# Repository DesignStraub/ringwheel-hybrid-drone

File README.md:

# Ringwheel – a drone whose prop ducts become wheels

A 5-inch FPV quadcopter that lands, folds its four ducts down by 90° and drives away on them. Each duct ring has a tread and turns into a wheel. The same four motors fly the drone and drive the wheels.

> **Status: design study.** Nothing here has been built, printed or flown yet. All dimensions, gear meshes and PCB traces are unverified until someone builds it. If you do, please open an issue and tell me what broke.

| Flight mode | Drive mode |
|---|---|
|  |  |

**Video:** [Watch the 55-second walkthrough on YouTube](https://www.youtube.com/shorts/o1WtWeNPCIw) or download it in 16:9 as [MP4](docs/video/ringwheel.mp4) (17 MB)

## How it works

- **Folding:** Each arm ends in a hinge. A small N20 gear motor turns it through a self-locking brass worm drive (1:30). An AS5600 magnetic sensor reads the angle, and fixed end stops limit the travel to 0° (flight) and 90° (drive).
- **Ring = wheel:** The duct around each 5.1" propeller has a TPU tread and runs on the hollow axle. In flight the ring is locked.
- **Drive train:** A sliding coupler on each motor axle switches between two positions. A solenoid coil pulls it one way, a spring pushes it back.
  - **Flight:** The coupler locks the wheel hub, so the ring stands still around the spinning prop.
  - **Drive:** The coupler engages the motor bell and drives the wheel through a 1:4 planetary stage (module 0.7, 24/24/72 teeth) inside the hub.
  - A Hall sensor (AH1806) and a small ring magnet confirm the coupler position.
- **Electronics:** A custom board (Hybrid-Controller HC-1, ESP32-S3) sits between the flight controller and the 4-in-1 ESC. A bus switch hands the four DShot signals either to the flight controller (flight) or to the ESP32 (drive). The board also runs the hinge motors and the solenoids. One small corner board per hinge (EP-1) carries the angle sensor and the wiring through the joint.
- **Safety logic:** Drive mode is only allowed while the flight controller reports *disarmed* and all four couplers report *engaged*. Folding only happens at standstill. See [electronics/README_Elektronik.md](electronics/README_Elektronik.md) (German) for the full sequence and pin map.

## Key data (from CAD)

| | |
|---|---|
| Props | 5.1" three-blade (Gemfan Hurricane 51466-3), duct inner Ø 130 mm |
| Motors | 4× 2306 2450 KV, 4S |
| Flight stack | 30 × 30 F722 + 55 A 4-in-1 ESC (Flywoo GOKU), ELRS receiver |
| Battery | 4S 1300 mAh |
| FPV | DJI O4 Air Unit Lite, camera in the wedge nose, tilted 15° |
| Hinge spacing | 170 × 160 mm |
| Mass | ≈ 950 g as modelled |
| Print materials | PA6-GF (frame, gears), TPU 95A (treads) |
| Parts cost | ≈ 910 € for the drone, ≈ 1,340 € including goggles, radio and charger (Germany, October 2026) |

## What is in this repository

| Path | Content |
|---|---|
| `cad/Drohne_Hybid_Car_v15.f3d` | Current Fusion design with joints and parameters (`klappwinkel` = fold angle, `muffe_weg` = coupler travel) |
| `cad/Drohne_Hybid_Car_v15.step` | The same assembly as STEP for other CAD tools |
| `cad/Drohne_Hybid_Car_v11_rounded_hull.f3d` | Older alternative with a rounded hull instead of the wedge nose |
| `electronics/` | KiCad 10 projects for HC-1 and EP-1, schematics as PDF, 3D models |
| `electronics/Fertigung/` | Gerber, BOM and placement files for JLCPCB |
| `docs/Kostenliste.md` | Full parts list with shop links and prices (German) |
| `docs/video/ringwheel.mp4` | Narrated walkthrough rendered from the Fusion model |

The detailed docs are in German for now. Translations are welcome.

## Open points before anyone builds it

- **Firmware:** not written yet. The ESP32 logic and the flight controller setup are only specified in the electronics README.
- **Flight performance:** untested. The ducts and the drive train add weight, so the thrust-to-weight ratio needs a real measurement.
- **Gear teeth:** module 0.7 in PA6-GF should print with a 0.4 mm nozzle, but this needs a test print.
- **Hall sensor:** the energised solenoid may trigger the sensor. This needs a bench test, which is why the firmware also checks the coupler via motor RPM.
- **Camera mount:** published dimensions of the O4 Lite camera disagree. The mount has slots to compensate, but check it against the real part.
- **PCBs:** routing was generated automatically and passes DRC, but review it in KiCad before ordering, especially USB and the power paths. Match the ESC connector pinout to the stack you buy.

## Credits

- Inspired by [Michael Rechtin's transforming drone](https://www.youtube.com/watch?v=f1GSzysrYtw). No files from his project are used here.
- CAD modelling, PCB layout and documentation were done with heavy AI assistance (Claude by Anthropic). That is one more reason to check every dimension before printing.
- Video narration generated with ElevenLabs (voice "Roger").
- Footprints and 3D models from the KiCad libraries remain under their own license. Product names belong to their respective owners.

## License

© 2026 DesignStraub. Licensed under [CC BY-NC-SA 4.0](LICENSE): you may build, modify and share this design for non-commercial purposes, as long as you give credit and share your changes under the same license.

**Additional permissions** granted by the author on top of the license:

- You may publish videos, photos and articles about your own build, including monetised ones (ads, sponsorships). This does not cover selling files, kits, parts or finished drones.
- Schools, universities, makerspaces and non-profit clubs may use the design for teaching and workshops, including fees that only cover material costs.
- **Commercial use** (selling kits, parts or built drones, or using the design in a product): please ask first by opening an issue.

## Safety and legal

This design is provided as is, without any warranty. Building, flying and driving it is entirely at your own risk.

- LiPo batteries can catch fire. Charge them under supervision and store them in a fireproof bag.
- The props sit on the drive motors, so they also spin in drive mode. Keep fingers out of the ducts.
- In the EU, a privately built drone of this weight falls into the open category, subcategory A3. You need to register as an operator, pass the A1/A3 online test, keep away from people and stay 150 m from residential areas. FPV flight requires an observer next to you. In Germany, liability insurance is mandatory. Check the rules in your country before the first flight.

---

## Kurz auf Deutsch

Eine 5-Zoll-FPV-Drohne, deren Propellerringe nach der Landung um 90° nach unten klappen und zu Rädern werden. Dieselben vier Motoren treiben beim Fahren über eine Schaltmuffe und ein Planetengetriebe 1:4 die Räder an. Das Projekt ist eine Konstruktionsstudie und noch nicht gebaut. Die ausführliche Doku zu Elektronik und Kosten ist auf Deutsch: [electronics/README_Elektronik.md](electronics/README_Elektronik.md) und [docs/Kostenliste.md](docs/Kostenliste.md).

Lizenz: CC BY-NC-SA 4.0 mit den oben genannten Zusatzerlaubnissen. Privat nachbauen und verändern ist ausdrücklich erwünscht. Für kommerzielle Nutzung bitte vorher fragen.

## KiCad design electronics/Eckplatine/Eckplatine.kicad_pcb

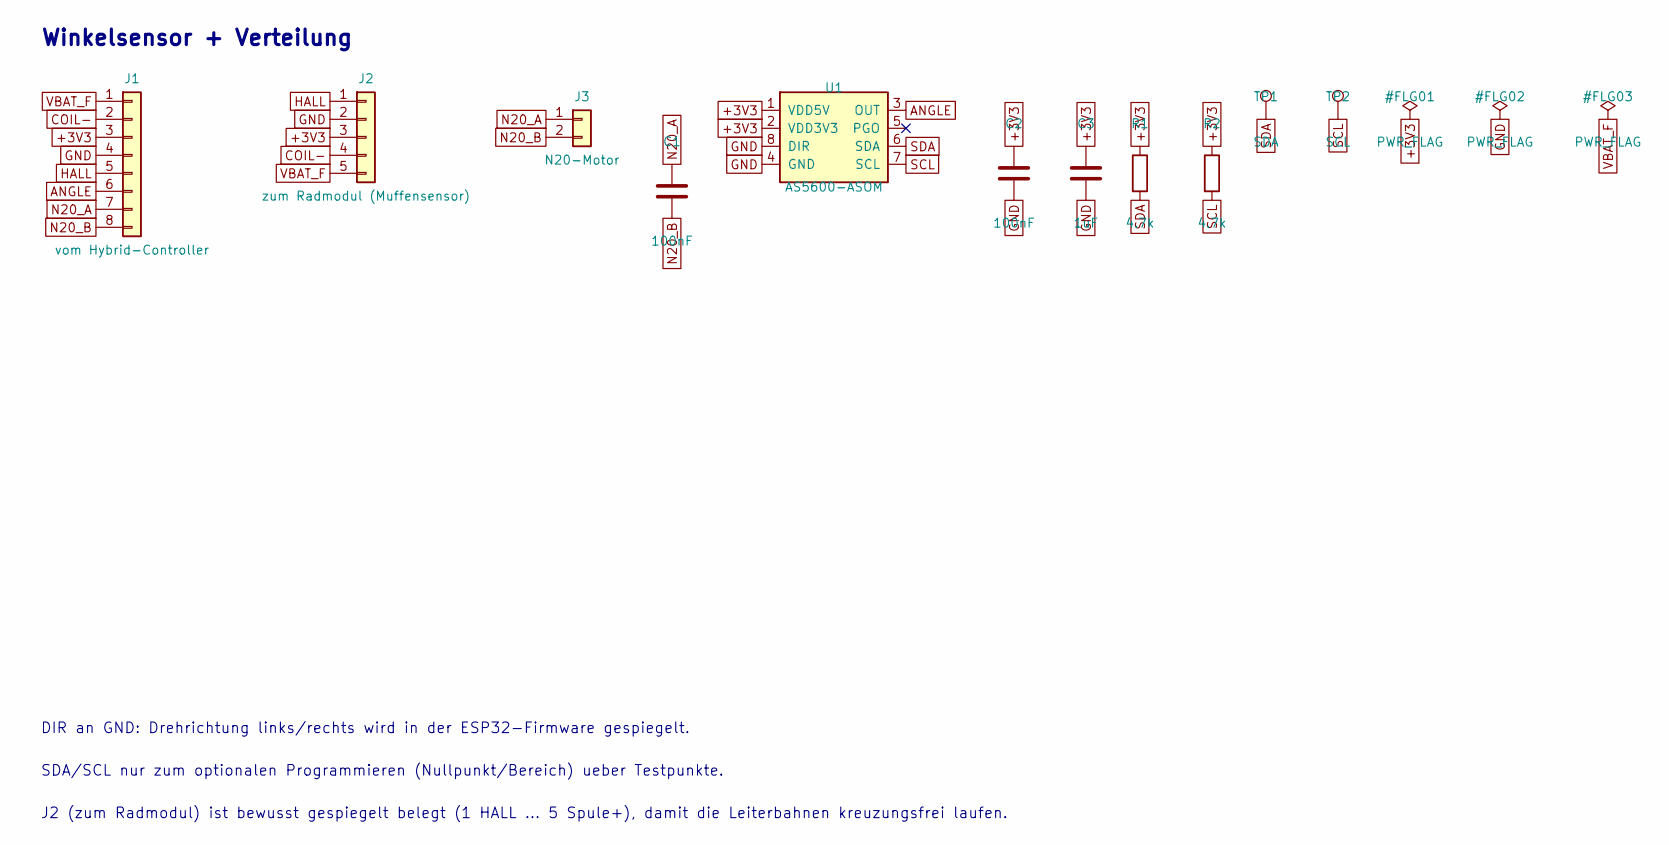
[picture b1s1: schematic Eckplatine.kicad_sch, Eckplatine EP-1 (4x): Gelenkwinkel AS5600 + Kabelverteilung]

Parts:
C1: 100nF; C_0603_1608Metric
C2: 100nF; C_0402_1005Metric
C3: 1uF; C_0402_1005Metric
J1: vom Hybrid-Controller; JST_GH_SM08B-GHS-TB_1x08-1MP_P1.25mm_Horizontal
J2: zum Radmodul (Muffensensor); JST_GH_SM05B-GHS-TB_1x05-1MP_P1.25mm_Horizontal
J3: N20-Motor; SolderWire-0.15sqmm_1x02_P4mm_D0.5mm_OD1.5mm
R1, R2: 4.7k; R_0402_1005Metric
TP1: SDA; TestPoint_Pad_D1.0mm
TP2: SCL; TestPoint_Pad_D1.0mm
U1: AS5600-ASOM; SOIC-8_3.9x4.9mm_P1.27mm

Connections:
+3V3: C2.1, C3.1, J1.3, J2.3, R1.1, R2.1, U1.1 (VDD5V), U1.2 (VDD3V3)
ANGLE: J1.6, U1.3 (OUT)
COIL-: J1.2, J2.4
GND: C2.2, C3.2, J1.4, J2.2, U1.4 (GND), U1.8 (DIR)
HALL: J1.5, J2.1
N20_A: C1.1, J1.7, J3.1
N20_B: C1.2, J1.8, J3.2
SCL: R2.2, TP2.1, U1.7 (SCL)
SDA: R1.2, TP1.1, U1.6 (SDA)
VBAT_F: J1.1, J2.5

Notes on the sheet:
Winkelsensor + Verteilung
J2 (zum Radmodul) ist bewusst gespiegelt belegt (1 HALL ... 5 Spule+), damit die Leiterbahnen kreuzungsfrei laufen.
DIR an GND: Drehrichtung links/rechts wird in der ESP32-Firmware gespiegelt.
SDA/SCL nur zum optionalen Programmieren (Nullpunkt/Bereich) ueber Testpunkte.

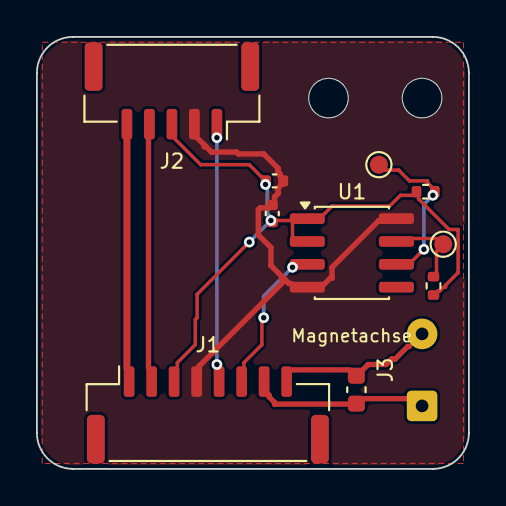
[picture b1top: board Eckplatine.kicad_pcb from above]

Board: 2 copper layers, 24.0 x 24.0 mm, 13 parts (0 on the bottom side), 10 nets.

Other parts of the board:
H1, H2: MountingHole_2.2mm_M2

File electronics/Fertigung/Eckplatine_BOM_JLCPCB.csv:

Comment,Designator,Footprint,LCSC Part #
100nF,C1,C_0603_1608Metric,
100nF,C2,C_0402_1005Metric,
1uF,C3,C_0402_1005Metric,
vom Hybrid-Controller,J1,JST_GH_SM08B-GHS-TB_1x08-1MP_P1.25mm_Horizontal,C265111
zum Radmodul (Muffensensor),J2,JST_GH_SM05B-GHS-TB_1x05-1MP_P1.25mm_Horizontal,C189896
4.7k,"R1,R2",R_0402_1005Metric,
AS5600-ASOM,U1,SOIC-8_3.9x4.9mm_P1.27mm,C79815

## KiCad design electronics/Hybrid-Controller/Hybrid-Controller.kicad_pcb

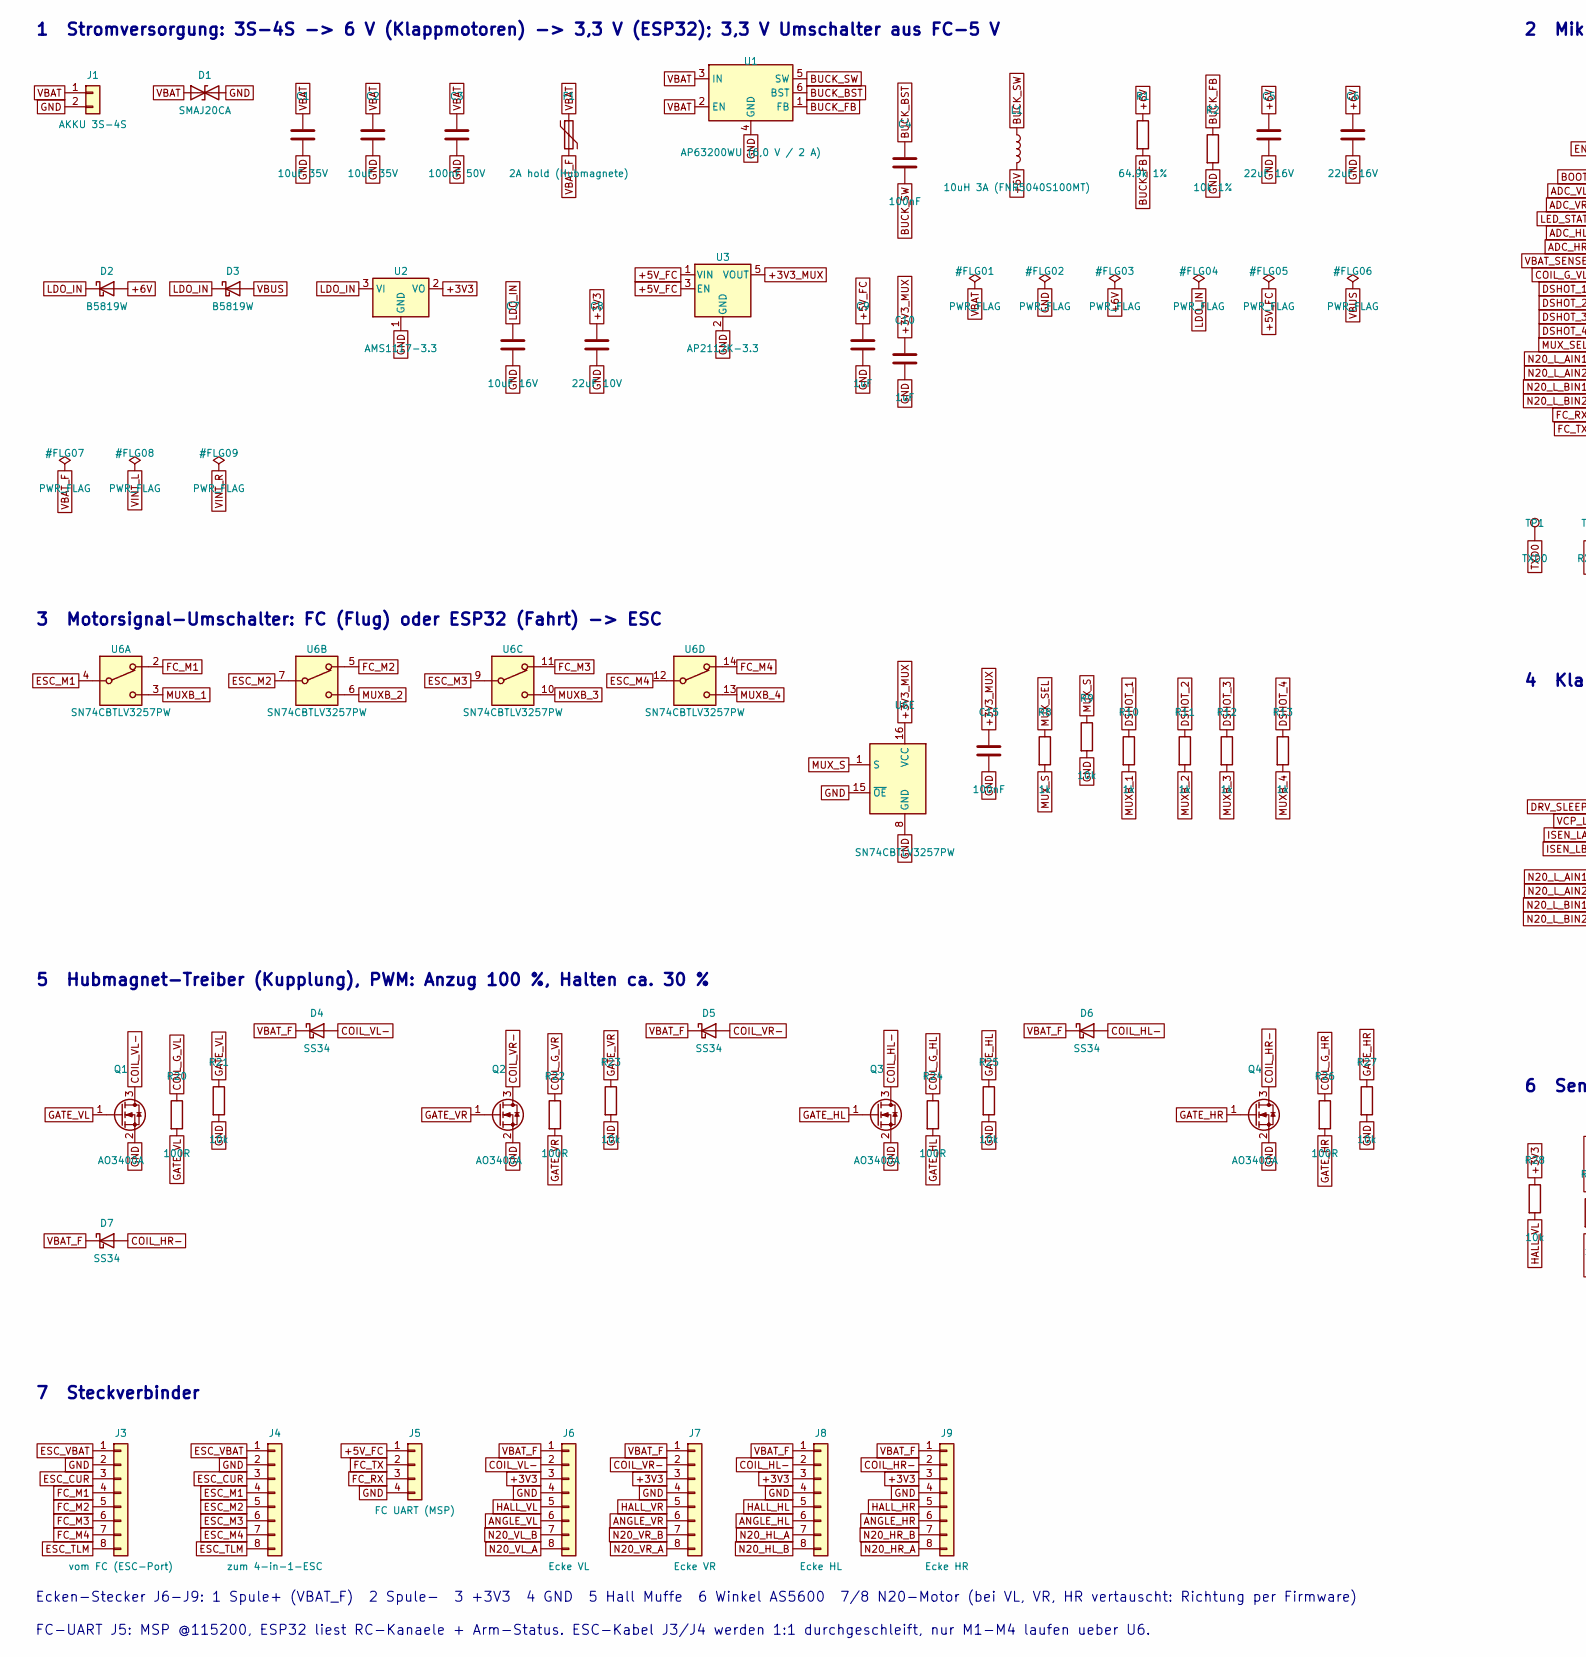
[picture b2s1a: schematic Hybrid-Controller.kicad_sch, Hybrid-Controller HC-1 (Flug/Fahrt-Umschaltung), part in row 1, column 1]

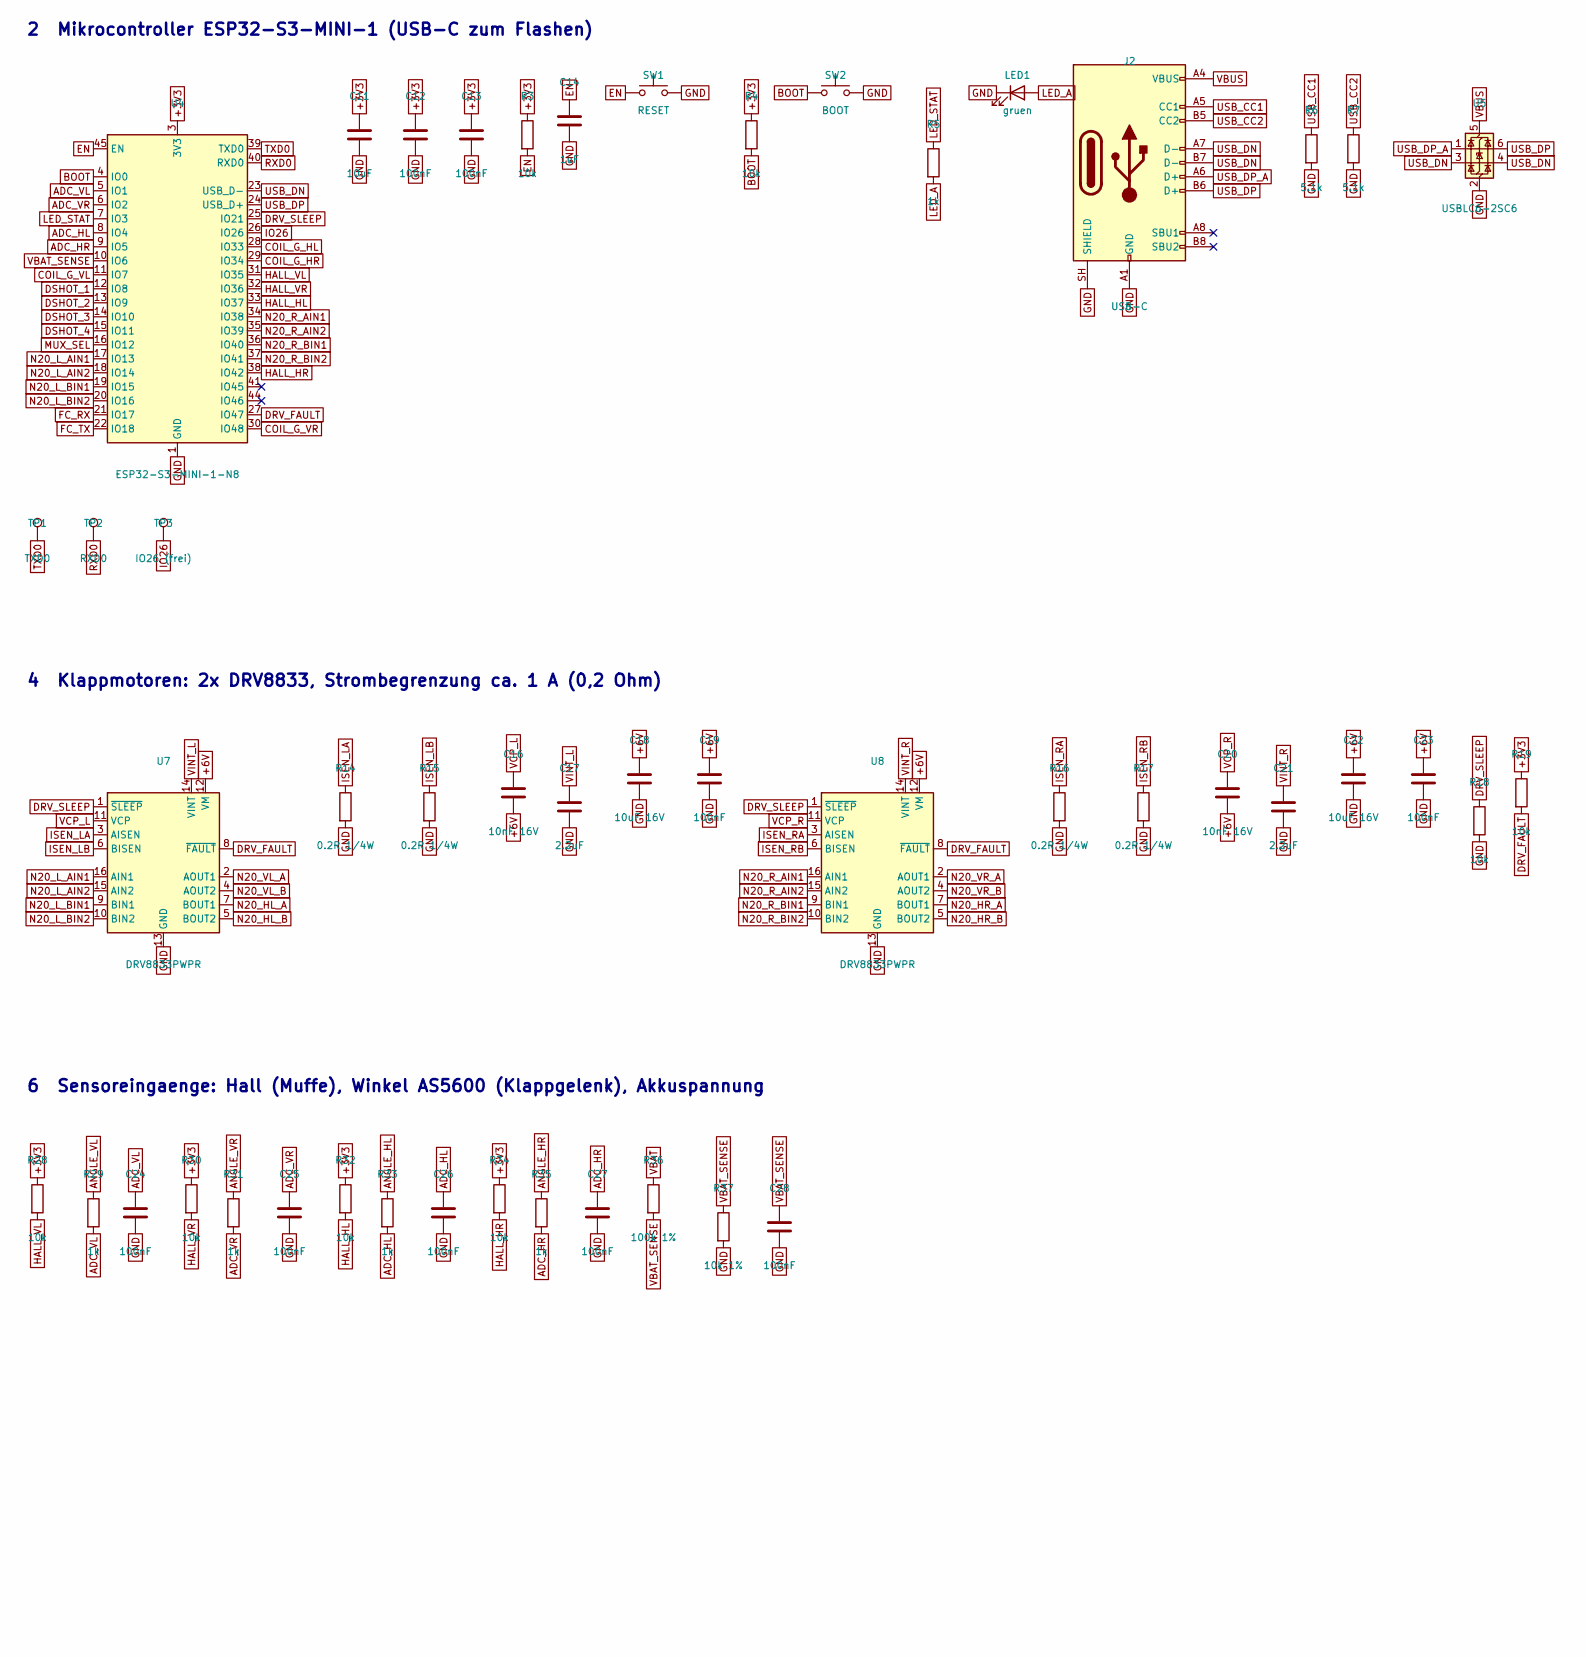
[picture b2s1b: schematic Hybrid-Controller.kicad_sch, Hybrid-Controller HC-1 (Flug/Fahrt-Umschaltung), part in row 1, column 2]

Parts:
C1, C2: 10uF 35V; C_1206_3216Metric
C3: 100nF 50V; C_0402_1005Metric
C4, C12, C13, C15, C19, C23, C24, C25, C26, C27, C28: 100nF; C_0402_1005Metric
C5, C6: 22uF 16V; C_1206_3216Metric
C7, C18, C22: 10uF 16V; C_0805_2012Metric
C8: 22uF 10V; C_0805_2012Metric
C9, C10, C14: 1uF; C_0603_1608Metric
C11: 10uF; C_0805_2012Metric
C16, C20: 10nF 16V; C_0402_1005Metric
C17, C21: 2.2uF; C_0603_1608Metric
D1: SMAJ20CA; D_SMA
D2, D3: B5819W; D_SOD-123
D4, D5, D6, D7: SS34; D_SMA
F1: 2A hold (Hubmagnete); Fuse_1812_4532Metric
J1: AKKU 3S-4S; SolderWire-0.5sqmm_1x02_P4.8mm_D0.9mm_OD2.3mm
J2: USB-C; USB_C_Receptacle_HRO_TYPE-C-31-M-12
J3: vom FC (ESC-Port); JST_SH_SM08B-SRSS-TB_1x08-1MP_P1.00mm_Horizontal
J4: zum 4-in-1-ESC; JST_SH_SM08B-SRSS-TB_1x08-1MP_P1.00mm_Horizontal
J5: FC UART (MSP); JST_SH_SM04B-SRSS-TB_1x04-1MP_P1.00mm_Horizontal
J6: Ecke VL; JST_GH_SM08B-GHS-TB_1x08-1MP_P1.25mm_Horizontal
J7: Ecke VR; JST_GH_SM08B-GHS-TB_1x08-1MP_P1.25mm_Horizontal
J8: Ecke HL; JST_GH_SM08B-GHS-TB_1x08-1MP_P1.25mm_Horizontal
J9: Ecke HR; JST_GH_SM08B-GHS-TB_1x08-1MP_P1.25mm_Horizontal
L1: 10uH 3A (FNR5040S100MT); L_Changjiang_FNR5040S
LED1: gruen; LED_0603_1608Metric
Q1, Q2, Q3, Q4: AO3400A; SOT-23
R1: 64.9k 1%; R_0402_1005Metric
R2, R37: 10k 1%; R_0402_1005Metric
R3, R4, R9, R18, R19, R21, R23, R25, R27, R28, R30, R32, R34: 10k; R_0402_1005Metric
R5, R8, R10, R11, R12, R13, R29, R31, R33, R35: 1k; R_0402_1005Metric
R6, R7: 5.1k; R_0402_1005Metric
R14, R15, R16, R17: 0.2R 1/4W; R_1206_3216Metric
R20, R22, R24, R26: 100R; R_0402_1005Metric
R36: 100k 1%; R_0402_1005Metric
SW1: RESET; SW_SPST_PTS810
SW2: BOOT; SW_SPST_PTS810
TP1: TXD0; TestPoint_Pad_D1.0mm
TP2: RXD0; TestPoint_Pad_D1.0mm
TP3: IO26 (frei); TestPoint_Pad_D1.0mm
U1: AP63200WU (6,0 V / 2 A); TSOT-23-6
U2: AMS1117-3.3; SOT-223-3_TabPin2
U3: AP2112K-3.3; SOT-23-5
U4: ESP32-S3-MINI-1-N8; ESP32-S2-MINI-1
U5: USBLC6-2SC6; SOT-23-6
U6: SN74CBTLV3257PW; TSSOP-16_4.4x5mm_P0.65mm
U7, U8: DRV8833PWPR; HTSSOP-16-1EP_4.4x5mm_P0.65mm_EP3.4x5mm_Mask2.46x2.31mm_The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

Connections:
+3V3: C8.1, C11.1, C12.1, C13.1, J6.3, J7.3, J8.3, J9.3, R3.1, R4.1, R19.1, R28.1, R30.1, R32.1, R34.1, U2.2 (VO), U4.3 (3V3)
+3V3_MUX: C10.1, C15.1, U3.5 (VOUT), U6.16 (VCC)
+5V_FC: C9.1, J5.1, U3.1 (VIN), U3.3 (EN)
+6V: C5.1, C6.1, C16.2, C18.1, C19.1, C20.2, C22.1, C23.1, D2.2 (A), L1.2, R1.1, U7.12 (VM), U8.12 (VM)
ADC_HL: C26.1, R33.2, U4.8 (IO4)
ADC_HR: C27.1, R35.2, U4.9 (IO5)
ADC_VL: C24.1, R29.2, U4.5 (IO1)
ADC_VR: C25.1, R31.2, U4.6 (IO2)
ANGLE_HL: J8.6, R33.1
ANGLE_HR: J9.6, R35.1
ANGLE_VL: J6.6, R29.1
ANGLE_VR: J7.6, R31.1
BOOT: R4.2, SW2.1, U4.4 (IO0)
BUCK_BST: C4.1, U1.6 (BST)
BUCK_FB: R1.2, R2.1, U1.1 (FB)
BUCK_SW: C4.2, L1.1, U1.5 (SW)
COIL_G_HL: R24.1, U4.28 (IO33)
COIL_G_HR: R26.1, U4.29 (IO34)
COIL_G_VL: R20.1, U4.11 (IO7)
COIL_G_VR: R22.1, U4.30 (IO48)
COIL_HL-: D6.2 (A), J8.2, Q3.3 (D)
COIL_HR-: D7.2 (A), J9.2, Q4.3 (D)
COIL_VL-: D4.2 (A), J6.2, Q1.3 (D)
COIL_VR-: D5.2 (A), J7.2, Q2.3 (D)
DRV_FAULT: R19.2, U4.27 (IO47), U7.8 (~FAULT), U8.8 (~FAULT)
DRV_SLEEP: R18.1, U4.25 (IO21), U7.1 (~SLEEP), U8.1 (~SLEEP)
DSHOT_1: R10.1, U4.12 (IO8)
DSHOT_2: R11.1, U4.13 (IO9)
DSHOT_3: R12.1, U4.14 (IO10)
DSHOT_4: R13.1, U4.15 (IO11)
EN: C14.1, R3.2, SW1.1, U4.45 (EN)
ESC_CUR: J3.3, J4.3
ESC_M1: J4.4, U6.4
ESC_M2: J4.5, U6.7
ESC_M3: J4.6, U6.9
ESC_M4: J4.7, U6.12
ESC_TLM: J3.8, J4.8
ESC_VBAT: J3.1, J4.1
FC_M1: J3.4, U6.2
FC_M2: J3.5, U6.5
FC_M3: J3.6, U6.11
FC_M4: J3.7, U6.14
FC_RX: J5.3, U4.21 (IO17)
FC_TX: J5.2, U4.22 (IO18)
GATE_HL: Q3.1 (G), R24.2, R25.1
GATE_HR: Q4.1 (G), R26.2, R27.1
GATE_VL: Q1.1 (G), R20.2, R21.1
GATE_VR: Q2.1 (G), R22.2, R23.1
GND: C1.2, C2.2, C3.2, C5.2, C6.2, C7.2, C8.2, C9.2, C10.2, C11.2, C12.2, C13.2, C14.2, C15.2, C17.2, C18.2, C19.2, C21.2, C22.2, C23.2, C24.2, C25.2, C26.2, C27.2, C28.2, D1.2 (A2), J1.2, J2.A1 (GND), J2.A12 (GND), J2.B1 (GND), J2.B12 (GND), J2.SH (SHIELD), J3.2, J4.2, J5.4, J6.4, J7.4, J8.4, J9.4, LED1.1 (K), Q1.2 (S), Q2.2 (S), Q3.2 (S), Q4.2 (S), R2.2, R6.2, R7.2, R9.2, R14.2, R15.2, R16.2, R17.2, R18.2, R21.2, R23.2, R25.2, R27.2, R37.2, SW1.2, SW2.2, U1.4 (GND), U2.1 (GND), U3.2 (GND), U4.1 (GND), U4.2 (GND), U4.42 (GND), U4.43 (GND), U4.46 (GND), U4.47 (GND), U4.48 (GND), U4.49 (GND), U4.50 (GND), U4.51 (GND), U4.52 (GND), U4.53 (GND), U4.54 (GND), U4.55 (GND), U4.56 (GND), U4.57 (GND), U4.58 (GND), U4.59 (GND), U4.60 (GND), U4.61 (GND), U4.62 (GND), U4.63 (GND), U4.64 (GND), U4.65 (GND), U5.2 (GND), U6.8 (GND), U6.15 (~OE), U7.13 (GND), U7.17 (GND), U8.13 (GND), U8.17 (GND)
HALL_HL: J8.5, R32.2, U4.33 (IO37)
HALL_HR: J9.5, R34.2, U4.38 (IO42)
HALL_VL: J6.5, R28.2, U4.31 (IO35)
HALL_VR: J7.5, R30.2, U4.32 (IO36)
IO26: TP3.1, U4.26 (IO26)
ISEN_LA: R14.1, U7.3 (AISEN)
ISEN_LB: R15.1, U7.6 (BISEN)
ISEN_RA: R16.1, U8.3 (AISEN)
ISEN_RB: R17.1, U8.6 (BISEN)
LDO_IN: C7.1, D2.1 (K), D3.1 (K), U2.3 (VI)
LED_A: LED1.2 (A), R5.2
LED_STAT: R5.1, U4.7 (IO3)
MUXB_1: R10.2, U6.3
MUXB_2: R11.2, U6.6
MUXB_3: R12.2, U6.10
MUXB_4: R13.2, U6.13
MUX_S: R8.2, R9.1, U6.1 (S)
MUX_SEL: R8.1, U4.16 (IO12)
N20_HL_A: J8.7, U7.7 (BOUT1)
N20_HL_B: J8.8, U7.5 (BOUT2)
N20_HR_A: J9.8, U8.7 (BOUT1)
N20_HR_B: J9.7, U8.5 (BOUT2)
N20_L_AIN1: U4.17 (IO13), U7.16 (AIN1)
N20_L_AIN2: U4.18 (IO14), U7.15 (AIN2)
N20_L_BIN1: U4.19 (IO15), U7.9 (BIN1)
N20_L_BIN2: U4.20 (IO16), U7.10 (BIN2)
N20_R_AIN1: U4.34 (IO38), U8.16 (AIN1)
N20_R_AIN2: U4.35 (IO39), U8.15 (AIN2)
N20_R_BIN1: U4.36 (IO40), U8.9 (BIN1)
N20_R_BIN2: U4.37 (IO41), U8.10 (BIN2)
N20_VL_A: J6.8, U7.2 (AOUT1)
N20_VL_B: J6.7, U7.4 (AOUT2)
N20_VR_A: J7.8, U8.2 (AOUT1)
N20_VR_B: J7.7, U8.4 (AOUT2)
RXD0: TP2.1, U4.40 (RXD0)
TXD0: TP1.1, U4.39 (TXD0)
USB_CC1: J2.A5 (CC1), R6.1
USB_CC2: J2.B5 (CC2), R7.1
USB_DN: J2.A7 (D-), J2.B7 (D-), U4.23 (USB_D-), U5.3 (I/O2), U5.4 (I/O2)
USB_DP: J2.B6 (D+), U4.24 (USB_D+), U5.6 (I/O1)
USB_DP_A: J2.A6 (D+), U5.1 (I/O1)
VBAT: C1.1, C2.1, C3.1, D1.1 (A1), F1.1, J1.1, R36.1, U1.2 (EN), U1.3 (IN)
VBAT_F: D4.1 (K), D5.1 (K), D6.1 (K), D7.1 (K), F1.2, J6.1, J7.1, J8.1, J9.1
VBAT_SENSE: C28.1, R36.2, R37.1, U4.10 (IO6)
VBUS: D3.2 (A), J2.A4 (VBUS), J2.A9 (VBUS), J2.B4 (VBUS), J2.B9 (VBUS), U5.5 (VBUS)
VCP_L: C16.1, U7.11 (VCP)
VCP_R: C20.1, U8.11 (VCP)
VINT_L: C17.1, U7.14 (VINT)
VINT_R: C21.1, U8.14 (VINT)

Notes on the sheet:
1 Stromversorgung: 3S-4S -> 6 V (Klappmotoren) -> 3,3 V (ESP32); 3,3 V Umschalter aus FC-5 V
2 Mikrocontroller ESP32-S3-MINI-1 (USB-C zum Flashen)
3 Motorsignal-Umschalter: FC (Flug) oder ESP32 (Fahrt) -> ESC
4 Klappmotoren: 2x DRV8833, Strombegrenzung ca. 1 A (0,2 Ohm)
5 Hubmagnet-Treiber (Kupplung), PWM: Anzug 100 %, Halten ca. 30 %
6 Sensoreingaenge: Hall (Muffe), Winkel AS5600 (Klappgelenk), Akkuspannung
7 Steckverbinder
Ecken-Stecker J6-J9: 1 Spule+ (VBAT_F) 2 Spule- 3 +3V3 4 GND 5 Hall Muffe 6 Winkel AS5600 7/8 N20-Motor (bei VL, VR, HR vertauscht: Richtung per Firmware)
FC-UART J5: MSP @115200, ESP32 liest RC-Kanaele + Arm-Status. ESC-Kabel J3/J4 werden 1:1 durchgeschleift, nur M1-M4 laufen ueber U6.

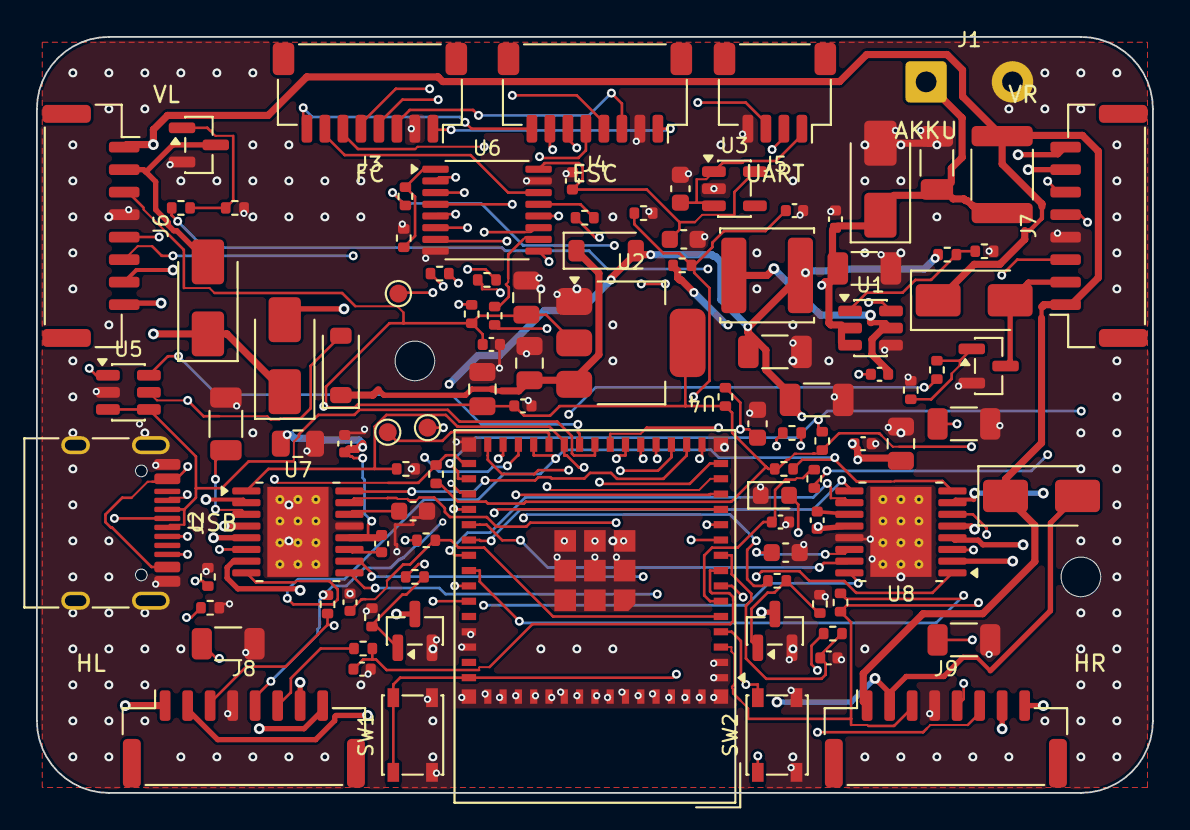
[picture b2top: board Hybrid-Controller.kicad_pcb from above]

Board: 4 copper layers, 62.0 x 42.0 mm, 103 parts (0 on the bottom side), 98 nets.

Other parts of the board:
H1, H2: MountingHole_2.2mm_M2

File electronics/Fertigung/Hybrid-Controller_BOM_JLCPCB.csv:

Comment,Designator,Footprint,LCSC Part #
10uF 35V,"C1,C2",C_1206_3216Metric,
10uF,C11,C_0805_2012Metric,
10nF 16V,"C16,C20",C_0402_1005Metric,
2.2uF,"C17,C21",C_0603_1608Metric,
100nF 50V,C3,C_0402_1005Metric,
100nF,"C4,C12,C13,C15,C19,C23,C24,C25,C26,C27,C28",C_0402_1005Metric,
22uF 16V,"C5,C6",C_1206_3216Metric,
10uF 16V,"C7,C18,C22",C_0805_2012Metric,
22uF 10V,C8,C_0805_2012Metric,
1uF,"C9,C10,C14",C_0603_1608Metric,
SMAJ20CA,D1,D_SMA,
B5819W,"D2,D3",D_SOD-123,
SS34,"D4,D5,D6,D7",D_SMA,C8678
2A hold (Hubmagnete),F1,Fuse_1812_4532Metric,
USB-C,J2,USB_C_Receptacle_HRO_TYPE-C-31-M-12,
vom FC (ESC-Port),J3,JST_SH_SM08B-SRSS-TB_1x08-1MP_P1.00mm_Horizontal,C160407
zum 4-in-1-ESC,J4,JST_SH_SM08B-SRSS-TB_1x08-1MP_P1.00mm_Horizontal,C160407
FC UART (MSP),J5,JST_SH_SM04B-SRSS-TB_1x04-1MP_P1.00mm_Horizontal,C160404
Ecke VL,J6,JST_GH_SM08B-GHS-TB_1x08-1MP_P1.25mm_Horizontal,C265111
Ecke VR,J7,JST_GH_SM08B-GHS-TB_1x08-1MP_P1.25mm_Horizontal,C265111
Ecke HL,J8,JST_GH_SM08B-GHS-TB_1x08-1MP_P1.25mm_Horizontal,C265111
Ecke HR,J9,JST_GH_SM08B-GHS-TB_1x08-1MP_P1.25mm_Horizontal,C265111
10uH 3A (FNR5040S100MT),L1,L_Changjiang_FNR5040S,
gruen,LED1,LED_0603_1608Metric,
AO3400A,"Q1,Q2,Q3,Q4",SOT-23,C20917
64.9k 1%,R1,R_0402_1005Metric,
0.2R 1/4W,"R14,R15,R16,R17",R_1206_3216Metric,
10k 1%,"R2,R37",R_0402_1005Metric,
100R,"R20,R22,R24,R26",R_0402_1005Metric,
10k,"R3,R4,R9,R18,R19,R21,R23,R25,R27,R28,R30,R32,R34",R_0402_1005Metric,
100k 1%,R36,R_0402_1005Metric,
1k,"R5,R8,R10,R11,R12,R13,R29,R31,R33,R35",R_0402_1005Metric,
5.1k,"R6,R7",R_0402_1005Metric,
RESET,SW1,SW_SPST_PTS810,
BOOT,SW2,SW_SPST_PTS810,
"AP63200WU (6,0 V / 2 A)",U1,TSOT-23-6,C2071868
AMS1117-3.3,U2,SOT-223-3_TabPin2,C6186
AP2112K-3.3,U3,SOT-23-5,C51118
ESP32-S3-MINI-1-N8,U4,ESP32-S2-MINI-1,C2913206
USBLC6-2SC6,U5,SOT-23-6,C7519
SN74CBTLV3257PW,U6,TSSOP-16_4.4x5mm_P0.65mm,C7637
DRV8833PWPR,"U7,U8",HTSSOP-16-1EP_4.4x5mm_P0.65mm_EP3.4x5mm_Mask2.46x2.31mm_ThermalVias,C50506
